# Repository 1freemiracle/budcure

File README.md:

# The Cannaster reinvisions the post-harvest workflow. The BudCureBox and Cannaster allows for automated control over the moisture content of the harvest, promising distinct differences in auroma and flavor. 

<div align="center">

</div>

## In the BudCureBox, you can estimate the moisture content by the weight loss due to evaporation. The weight is tracked from harvest and a target weight is calculated. This weight is used to know when to take the nugs off the branch and put into the Cannaster, when about 65% of the initial weight is lost.

<div align="center">

</div>

> The BudCure Box provides a stable environment for the buds to slowly dry. 

## The Cannaster takes mostly dry nugs and gets them to the perfect moisture content for canning. The vacuum brings moisture out from inside the nugs, drying them quickly and evenly to a precise moisture content. 

<div align="center">

</div>
> The Cannaster dials in the moisture content of the buds in preparation for canning.

## The machines are built out of laser cut or 3D printed parts, and I have included up to date files on how to build one, including eagle PCB and fusion 360 files.

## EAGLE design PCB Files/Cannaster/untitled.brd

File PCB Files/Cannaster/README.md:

# PCB files for the Cannaster
## 4 stepper motors plug directly into the board, with the L293D stepper driver chip. I'm also plugging into i2c humidity and pressure sensor, the BMP280 + AHT20, along with an OLED with rotary encoder display. The cannaster is powered by the wemos d1 mini.

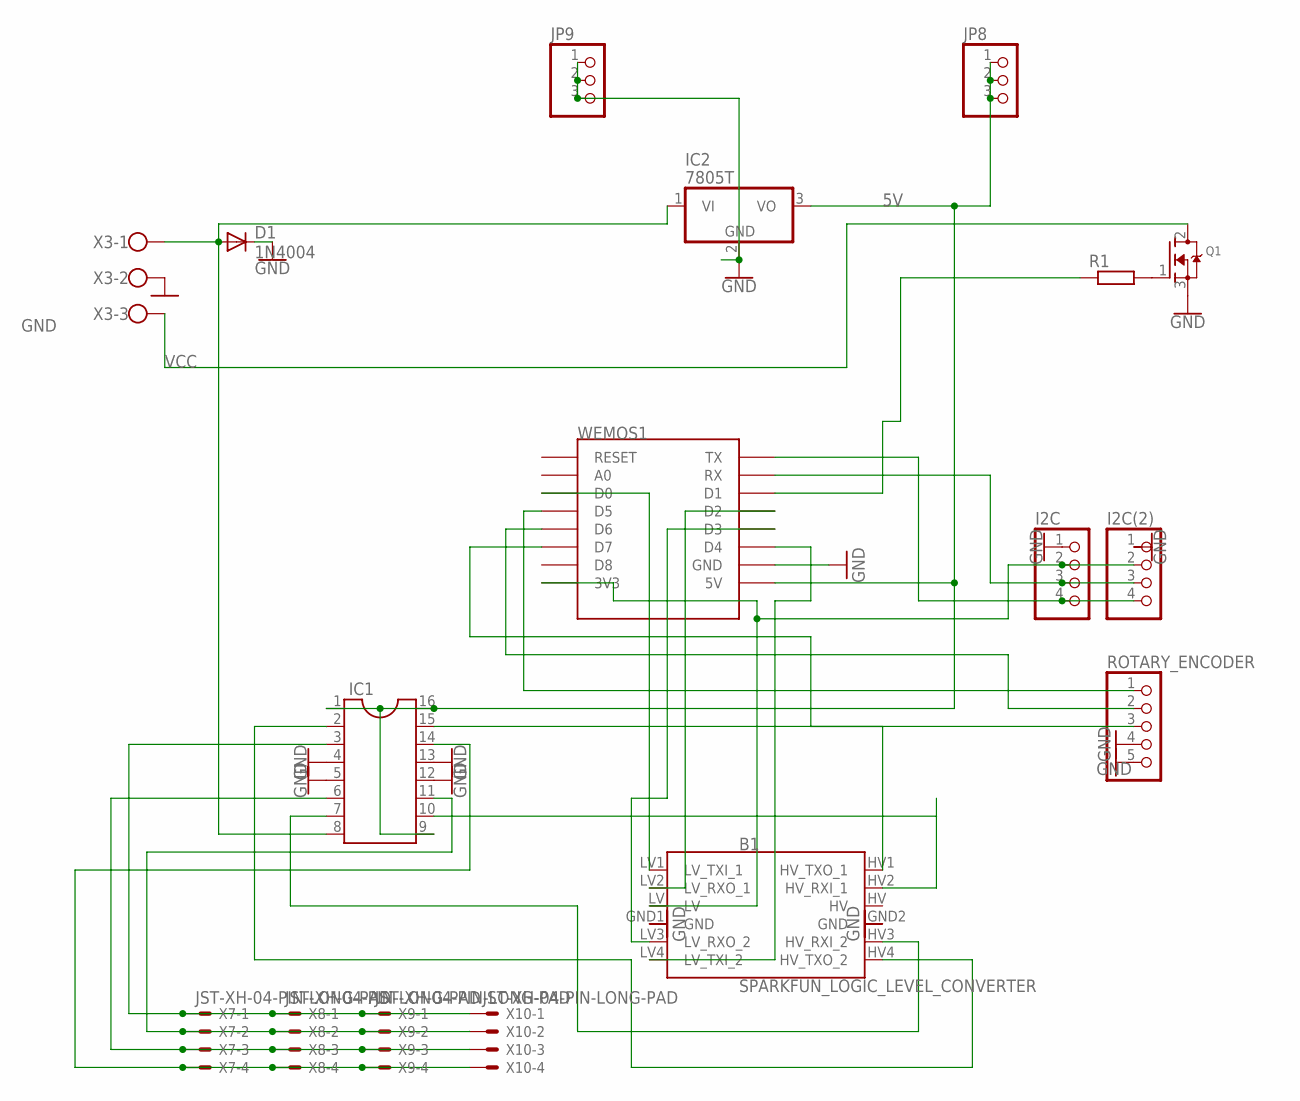
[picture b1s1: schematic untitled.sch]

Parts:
B1: SPARKFUN_LOGIC_LEVEL_CONVERTER
D1: 1N4004; DO41-10
I2C, I2C(2): PINHD-1X4; 1X04
IC1: DIL16
IC2: 7805T; TO220H
JP8, JP9: PINHD-1X3; 1X03
Q1: MOSFET-NGDS_TO220V; TO220V
R1: R-EU_0207/7; 0207/7
ROTARY_ENCODER: PINHD-1X5; 1X05
WEMOS1: WEMOS-D1-MINI
X3: W237-103
X7, X8, X9, X10: JST-XH-04-PIN-LONG-PAD; JST-XH-04-PACKAGE-LONG-PAD

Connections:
5V: IC1.1, IC1.9, IC1.16, IC2.3 (VO), JP8.1, JP8.2, JP8.3, WEMOS1.5V
GND: B1.GND1 (GND), B1.GND2 (GND), D1.C, I2C.1, I2C(2).1, IC1.4, IC1.5, IC1.12, IC1.13, IC2.2 (GND), JP9.1, JP9.2, JP9.3, Q1.3 (S), ROTARY_ENCODER.4, ROTARY_ENCODER.5, WEMOS1.GND, X3.2
HV: B1.HV
unnamed: IC1.3, X7.1, X8.1, X9.1, X10.1
unnamed: IC1.11, X7.2, X8.2, X9.2, X10.2
unnamed: B1.HV1 (HV_TXO_1), IC1.15
unnamed: IC1.14, X7.4, X8.4, X9.4, X10.4
unnamed: B1.LV1 (LV_TXI_1), WEMOS1.D0
unnamed: Q1.2 (D), X3.3
unnamed: I2C.4, I2C(2).4, WEMOS1.TX
unnamed: I2C.3, I2C(2).3, WEMOS1.RX
unnamed: B1.LV2 (LV_RXO_1), WEMOS1.D2
unnamed: Q1.1 (G), R1.2
unnamed: B1.LV3 (LV_RXO_2), WEMOS1.D3
unnamed: B1.LV4 (LV_TXI_2), WEMOS1.D4
unnamed: ROTARY_ENCODER.1, WEMOS1.D5
unnamed: ROTARY_ENCODER.2, WEMOS1.D6
unnamed: ROTARY_ENCODER.3, WEMOS1.D7
unnamed: R1.1, WEMOS1.D1
unnamed: B1.LV, I2C.2, I2C(2).2, WEMOS1.3V3
unnamed: B1.HV2 (HV_RXI_1), IC1.10
unnamed: B1.HV3 (HV_RXI_2), IC1.7
unnamed: B1.HV4 (HV_TXO_2), IC1.2
unnamed: IC1.6, X7.3, X8.3, X9.3, X10.3
VCC: D1.A, IC1.8, IC2.1 (VI), X3.1

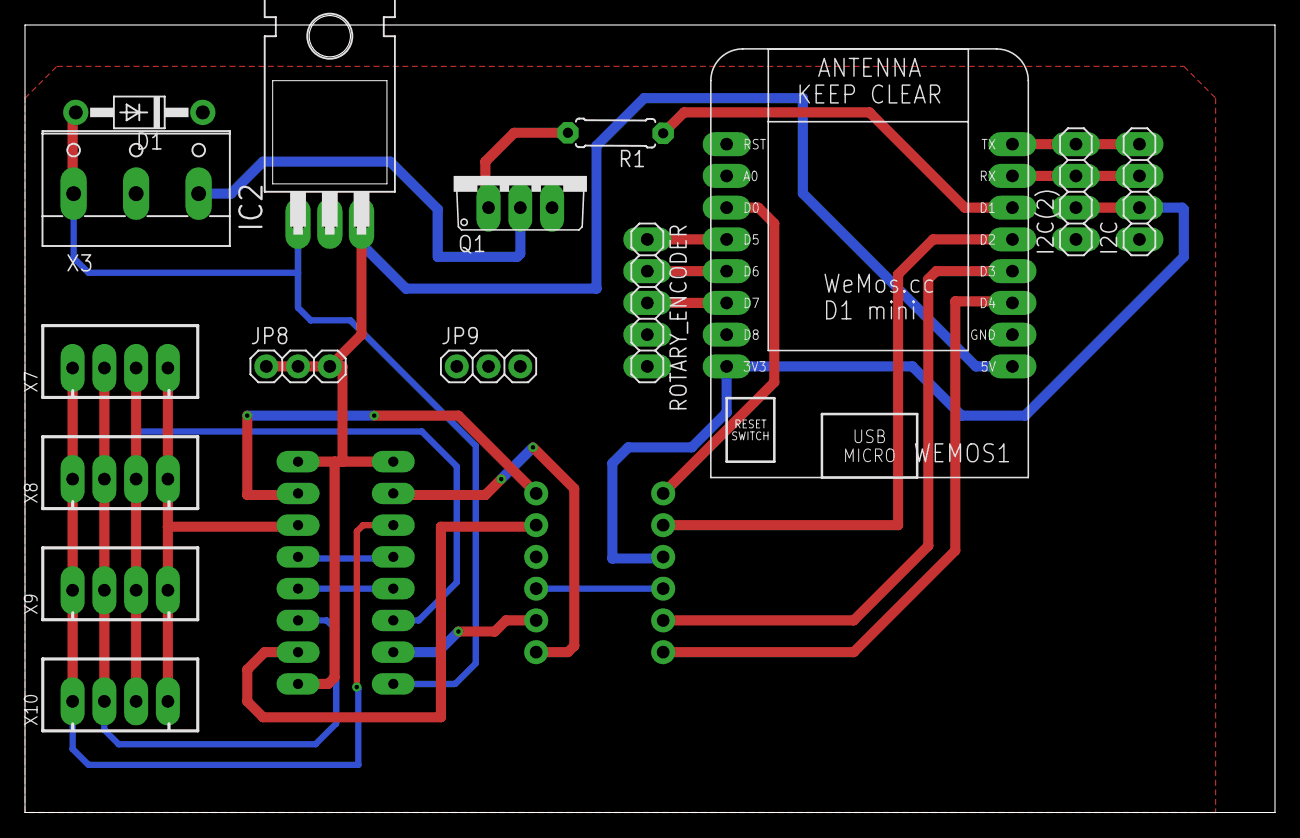
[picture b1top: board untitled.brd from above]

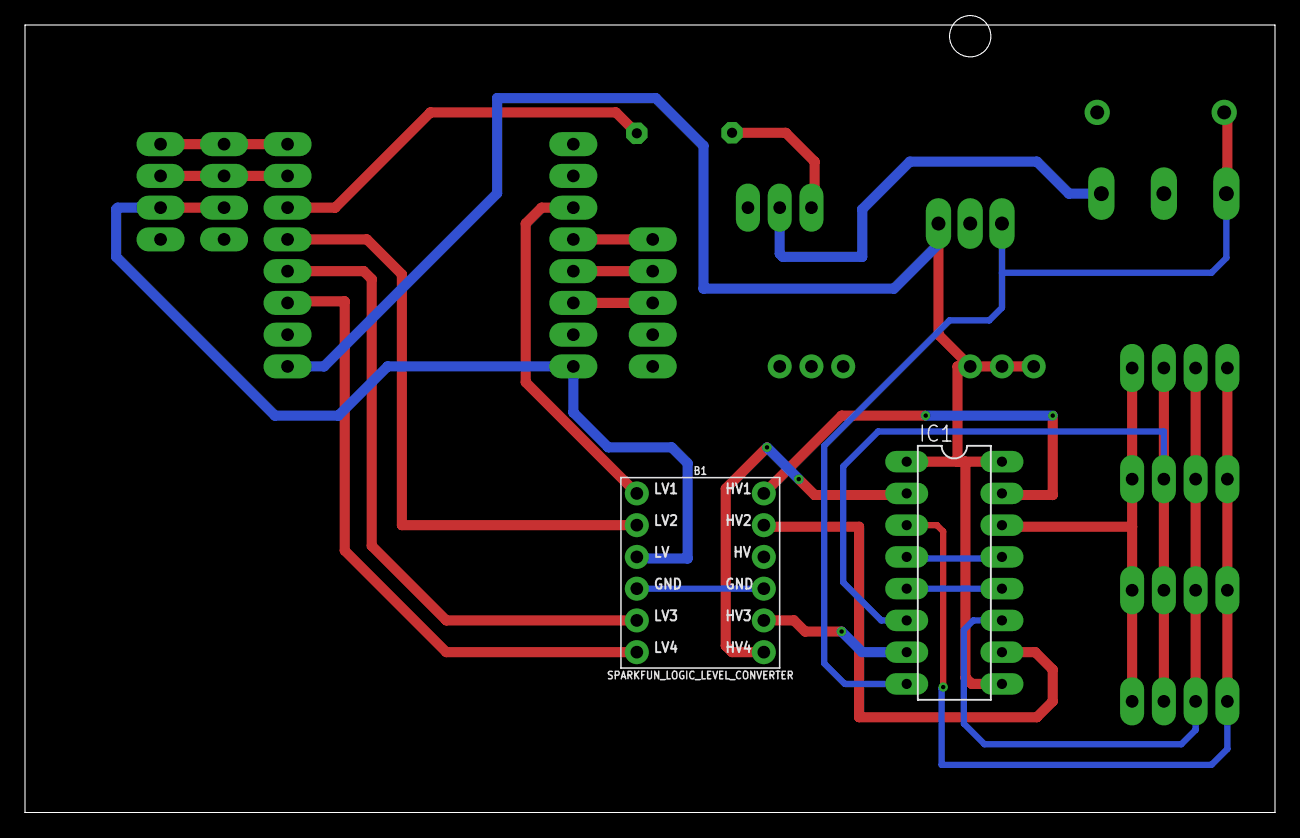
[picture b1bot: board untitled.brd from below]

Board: 2 copper layers, 100.0 x 63.0 mm, 17 parts (2 on the bottom side), 24 nets.

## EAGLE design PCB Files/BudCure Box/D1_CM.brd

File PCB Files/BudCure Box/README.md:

# PCB for the BudCure Box
## The BudCure Box pcb utilizes two mosfets, OLED/rotary encoder, i2c humidity sensor, load cell (with hx711), and a one wire temperature sensor for the TEC. 12V power runs the TEC and the fan while a 5v regulator supplies the Wemos.

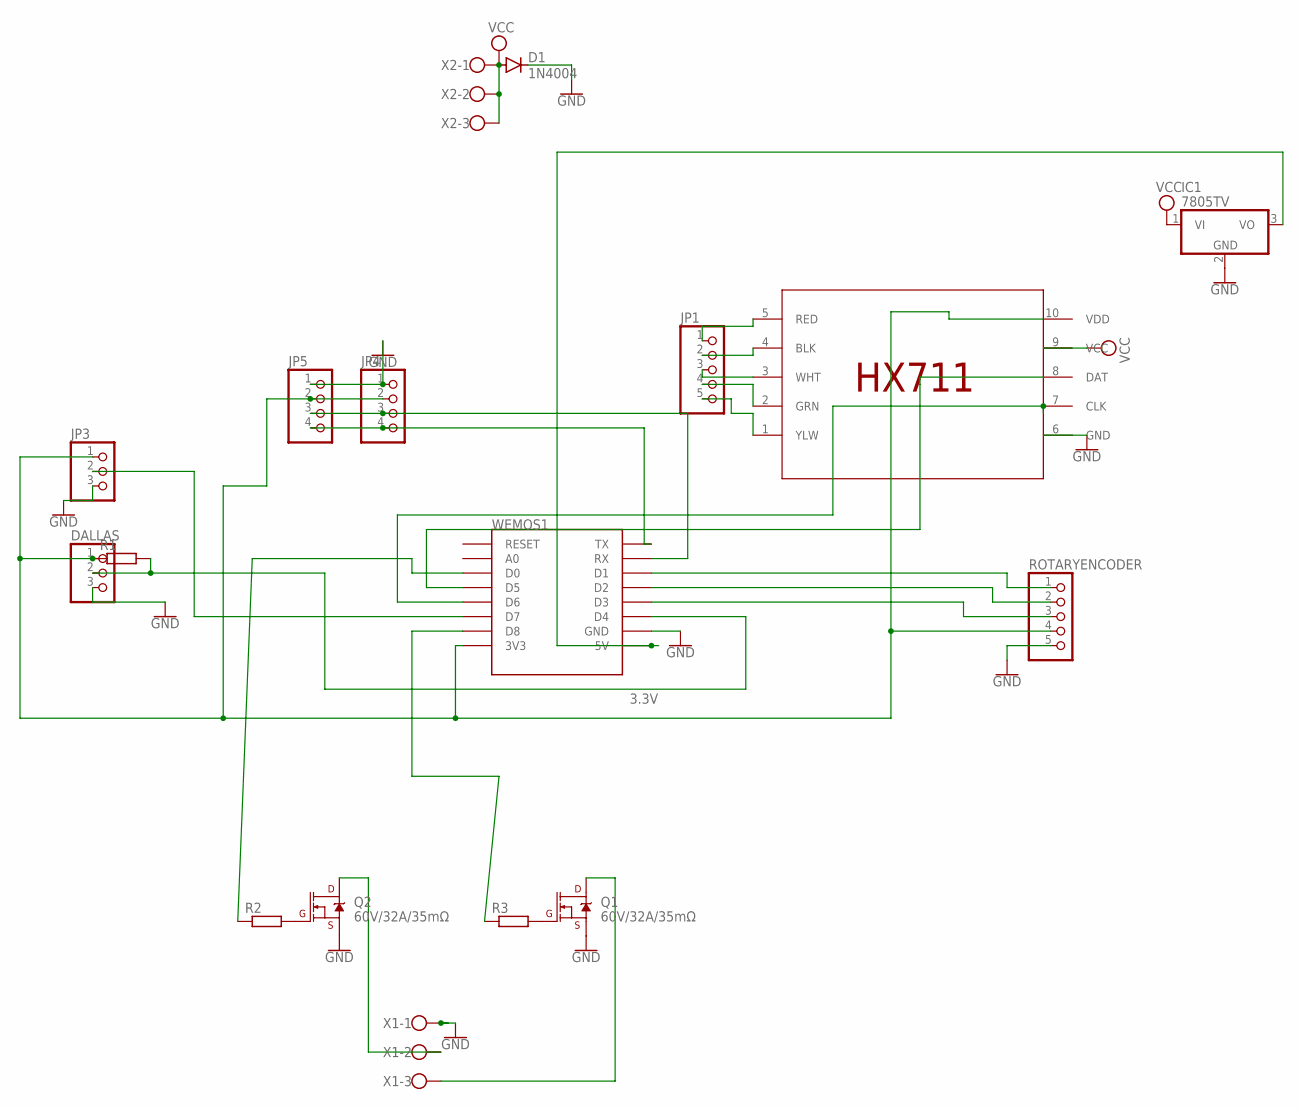
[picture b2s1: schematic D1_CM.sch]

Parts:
D1: 1N4004; DO41-10
DALLAS: PINHD-1X3; 1X03
IC1: 7805TV; TO220V
JP1: PINHD-1X5; 1X05
JP3: PINHD-1X3; 1X03
JP4, JP5: PINHD-1X4; 1X04
Q1, Q2: 60V/32A/35mΩ; TO220V
R1, R2, R3: R-EU_0207/7; 0207/7
ROTARYENCODER: PINHD-1X5; 1X05
U$1: DEVICY; FOOTSY
WEMOS1: WEMOS-D1-MINI
X1, X2: W237-103

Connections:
3.3V: DALLAS.1, JP3.1, JP4.2, JP5.2, R1.1, ROTARYENCODER.4, U$1.10 (VDD), WEMOS1.3V3
GND: D1.C, DALLAS.3, IC1.2 (GND), JP3.3, JP4.1, JP5.1, Q1.3 (S), Q2.3 (S), ROTARYENCODER.5, U$1.6 (GND), WEMOS1.GND, X1.1
unnamed: JP1.1, U$1.5 (RED)
unnamed: JP1.2, U$1.4 (BLK)
unnamed: JP1.3, U$1.3 (WHT)
unnamed: JP1.4, U$1.2 (GRN)
unnamed: JP1.5, U$1.1 (YLW)
unnamed: DALLAS.2, R1.2, WEMOS1.D4
unnamed: Q2.1 (G), R2.2
unnamed: JP4.3, JP5.3, WEMOS1.RX
unnamed: JP4.4, JP5.4, WEMOS1.TX
unnamed: Q1.1 (G), R3.2
unnamed: ROTARYENCODER.2, WEMOS1.D2
unnamed: ROTARYENCODER.1, WEMOS1.D1
unnamed: R2.1, WEMOS1.D0
unnamed: R3.1, WEMOS1.D8
unnamed: Q2.2 (D), X1.2
unnamed: Q1.2 (D), X1.3
unnamed: U$1.8 (DAT), WEMOS1.D5
unnamed: U$1.7 (CLK), WEMOS1.D6
unnamed: JP3.2, WEMOS1.D7
unnamed: ROTARYENCODER.3, WEMOS1.D3
unnamed: IC1.3 (VO), WEMOS1.5V
VCC: D1.A, IC1.1 (VI), U$1.9 (VCC), X2.1, X2.2, X2.3

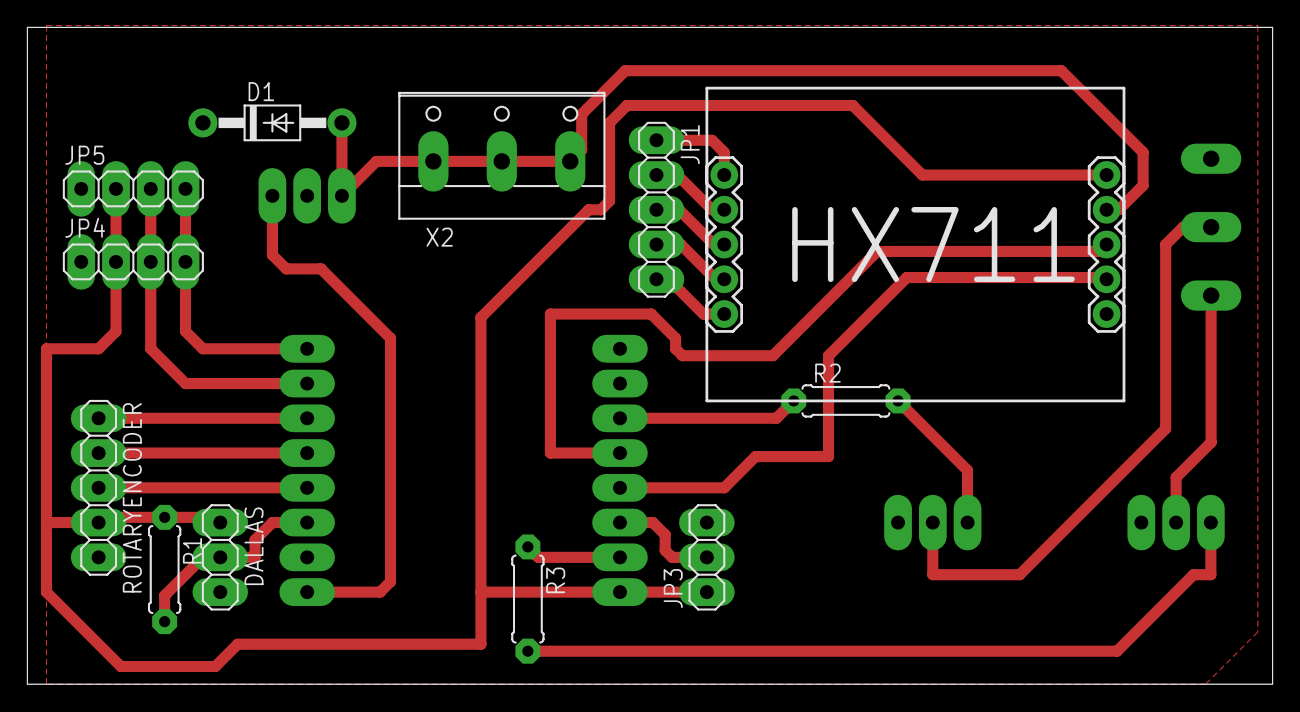
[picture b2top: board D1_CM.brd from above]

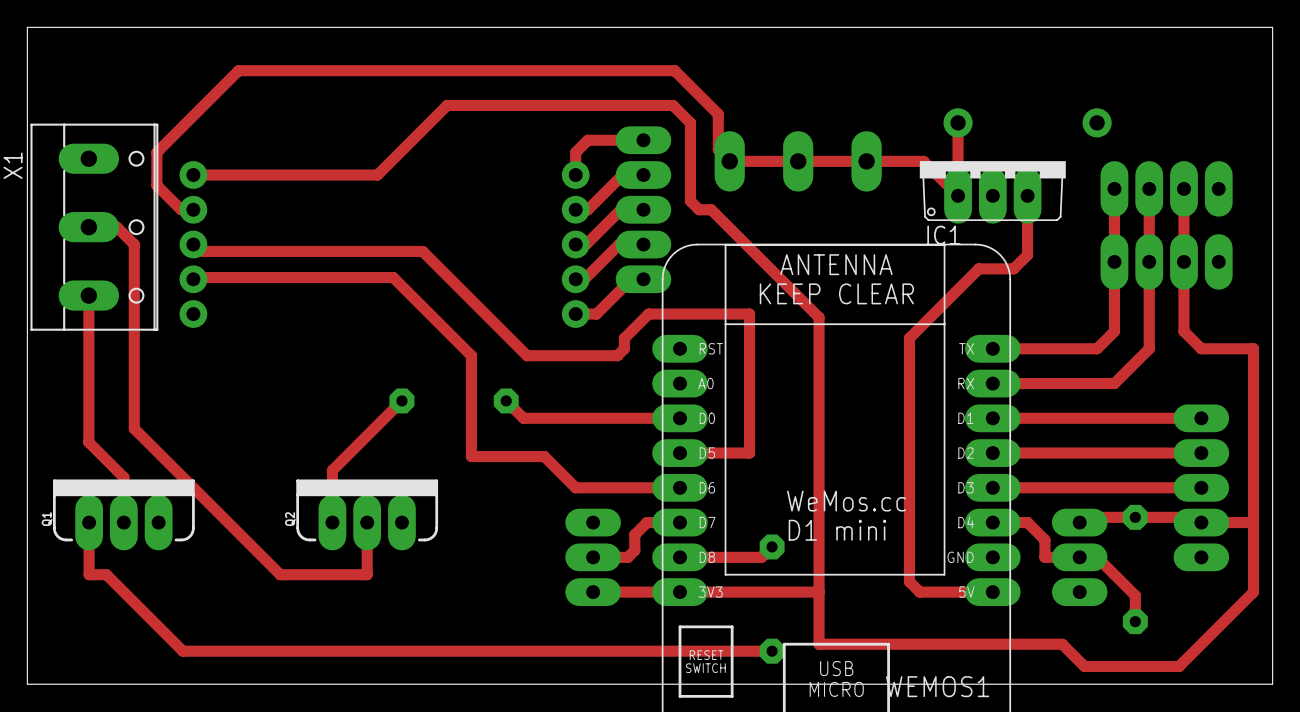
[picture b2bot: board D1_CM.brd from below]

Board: 2 copper layers, 91.0 x 48.0 mm, 17 parts (5 on the bottom side), 24 nets.

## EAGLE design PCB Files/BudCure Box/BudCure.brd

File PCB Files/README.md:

# EAGLE CAD FILES
## The BudCure Box and Cannaster utilize the Arduino Nano.

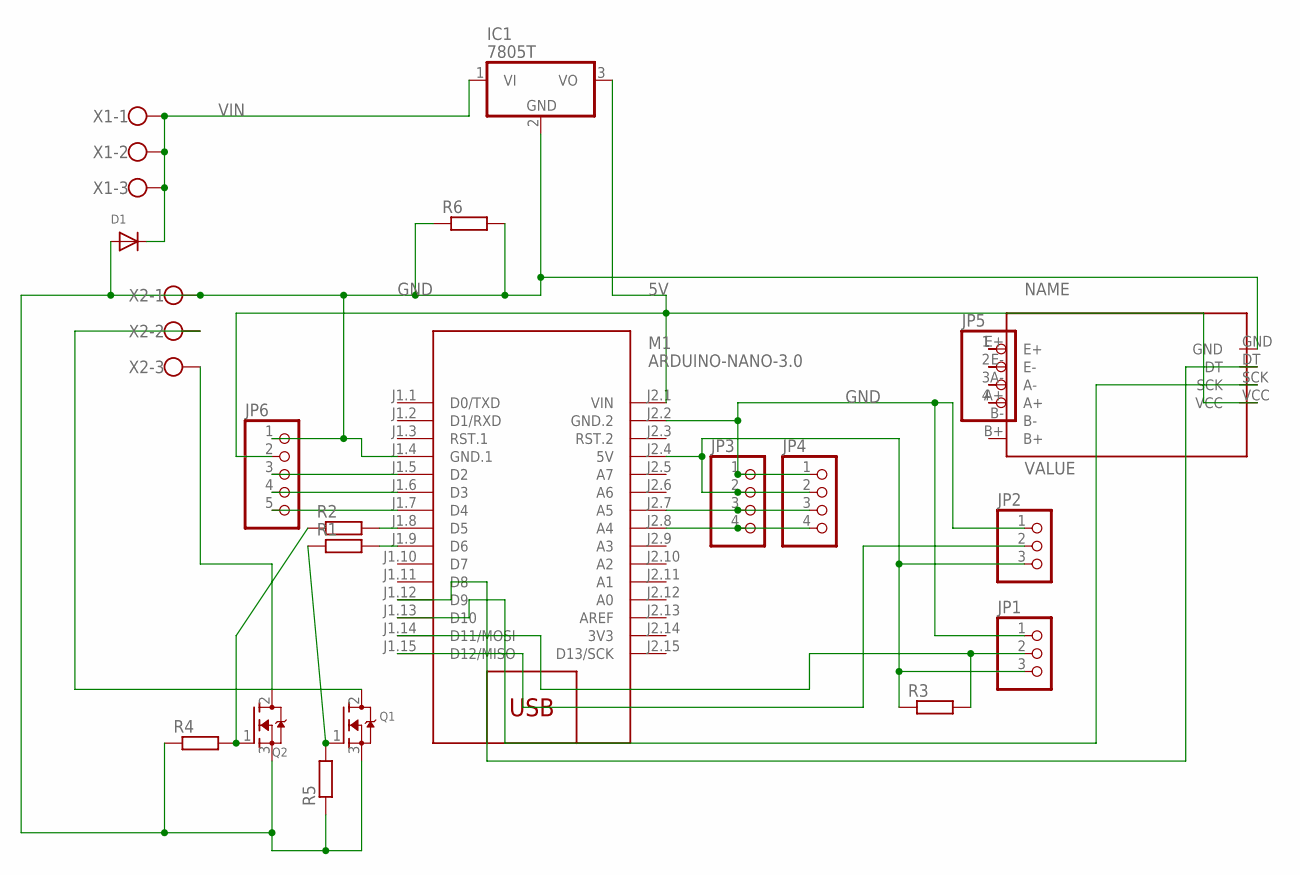
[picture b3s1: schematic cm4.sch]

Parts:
D1: DIODEDO-1N4148; DO-1N4148
IC1: 7805T; TO220H
JP1, JP2: PINHD-1X3; 1X03
JP3, JP4, JP5: PINHD-1X4; 1X04
JP6: PINHD-1X5; 1X05
M1: ARDUINO-NANO-3.0
Q1, Q2: MOSFET-NGDS_TO220V; TO220V
R1, R2, R3, R4, R5, R6: R-EU_0207/7; 0207/7
U$1: HX711A; HX711
X1, X2: W237-103

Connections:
3V3: M1.J2.14 (3V3)
5V: IC1.3 (VO), JP6.2, M1.J2.1 (VIN), U$1.VCC
GND: D1.A, IC1.2 (GND), JP1.1, JP2.1, JP3.1, JP4.1, JP6.1, M1.J1.4 (GND.1), M1.J2.2 (GND.2), Q1.3 (S), Q2.3 (S), R4.1, R5.1, R6.1, R6.2, U$1.GND, X2.1
unnamed: M1.J1.8 (D5), R2.2
unnamed: M1.J1.9 (D6), R1.2
unnamed: JP6.3, M1.J1.5 (D2)
unnamed: JP6.4, M1.J1.6 (D3)
unnamed: JP5.1, U$1.E+
unnamed: JP5.2, U$1.E-
unnamed: JP1.3, JP2.3, JP3.2, JP4.2, M1.J2.4 (5V), R3.1
unnamed: Q1.1 (G), R1.1, R5.2
unnamed: Q2.1 (G), R2.1, R4.2
unnamed: Q2.2 (D), X2.3
unnamed: Q1.2 (D), X2.2
unnamed: JP6.5, M1.J1.7 (D4)
unnamed: JP5.3, U$1.A-
unnamed: JP5.4, U$1.A+
unnamed: M1.J1.12 (D9), U$1.DT
unnamed: M1.J1.13 (D10), U$1.SCK
unnamed: JP3.3, JP4.3, M1.J2.7 (A5)
unnamed: JP3.4, JP4.4, M1.J2.8 (A4)
unnamed: JP1.2, M1.J1.14 (D11/MOSI), R3.2
unnamed: JP2.2, M1.J1.15 (D12/MISO)
VIN: D1.C, IC1.1 (VI), X1.1, X1.2, X1.3

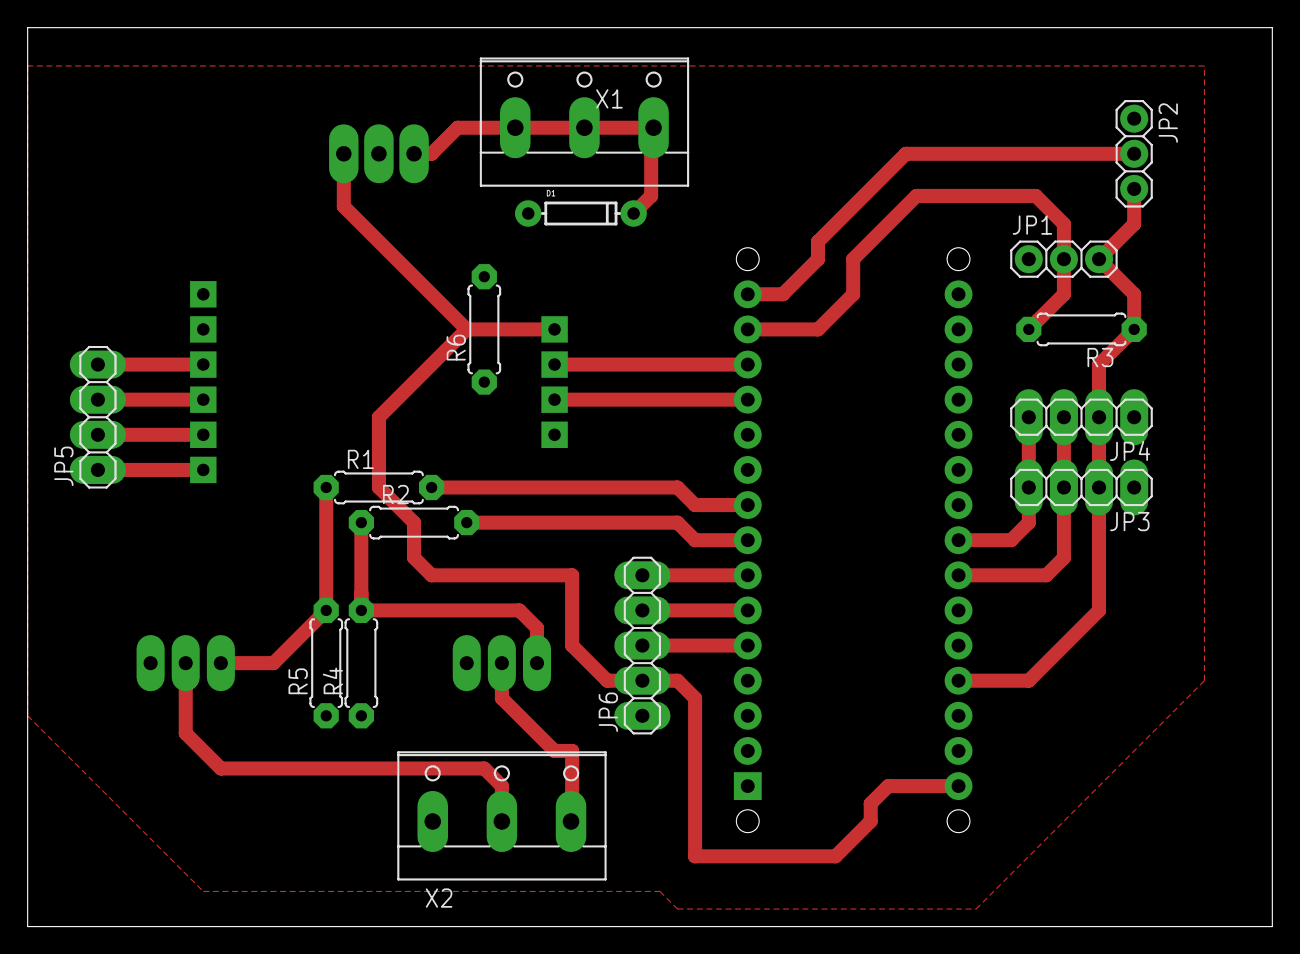
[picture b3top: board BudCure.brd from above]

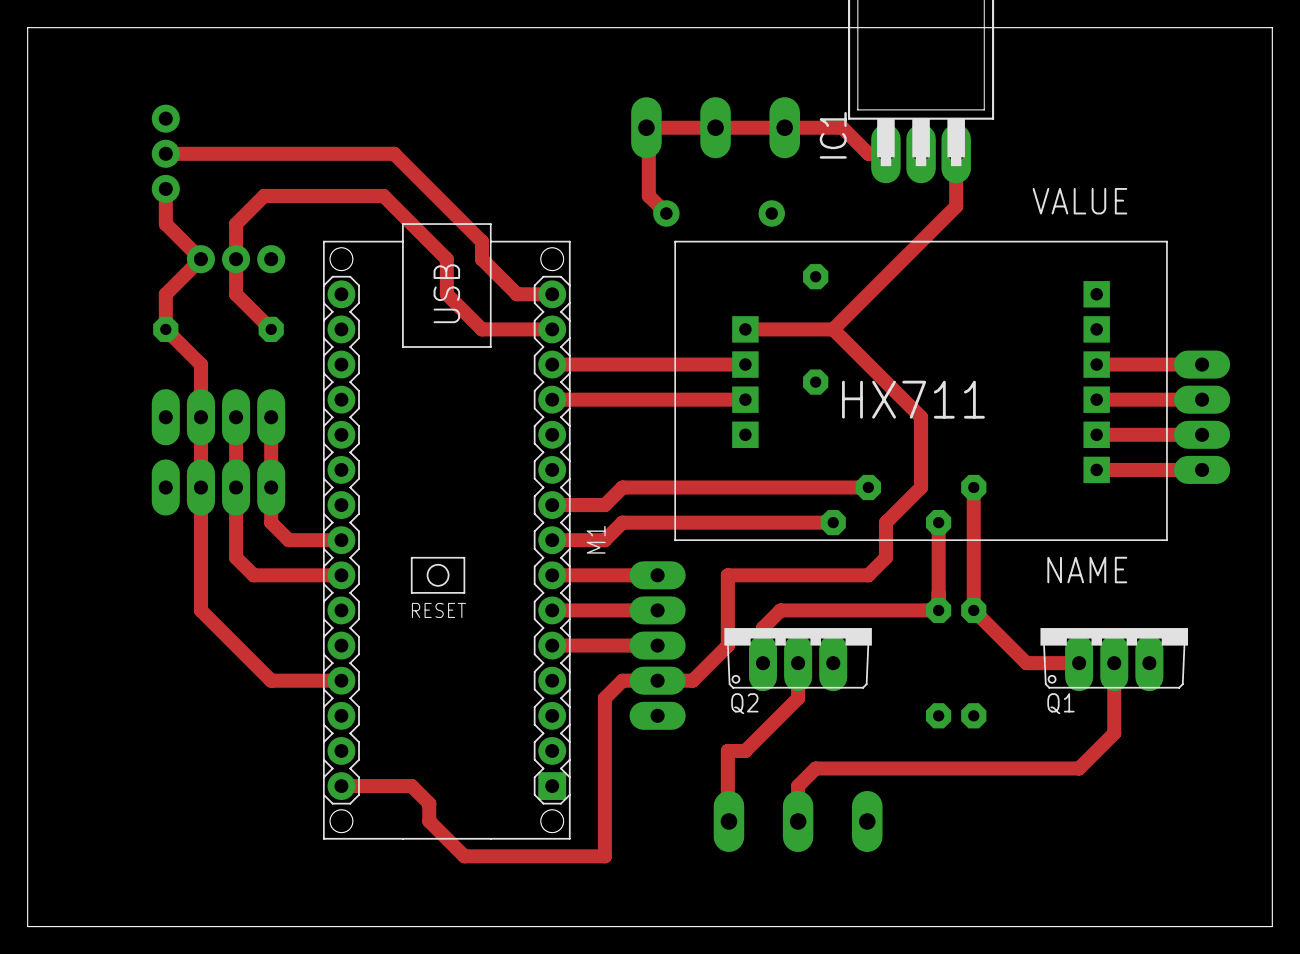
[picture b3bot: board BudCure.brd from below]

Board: 2 copper layers, 90.0 x 65.0 mm, 20 parts (5 on the bottom side), 23 nets.

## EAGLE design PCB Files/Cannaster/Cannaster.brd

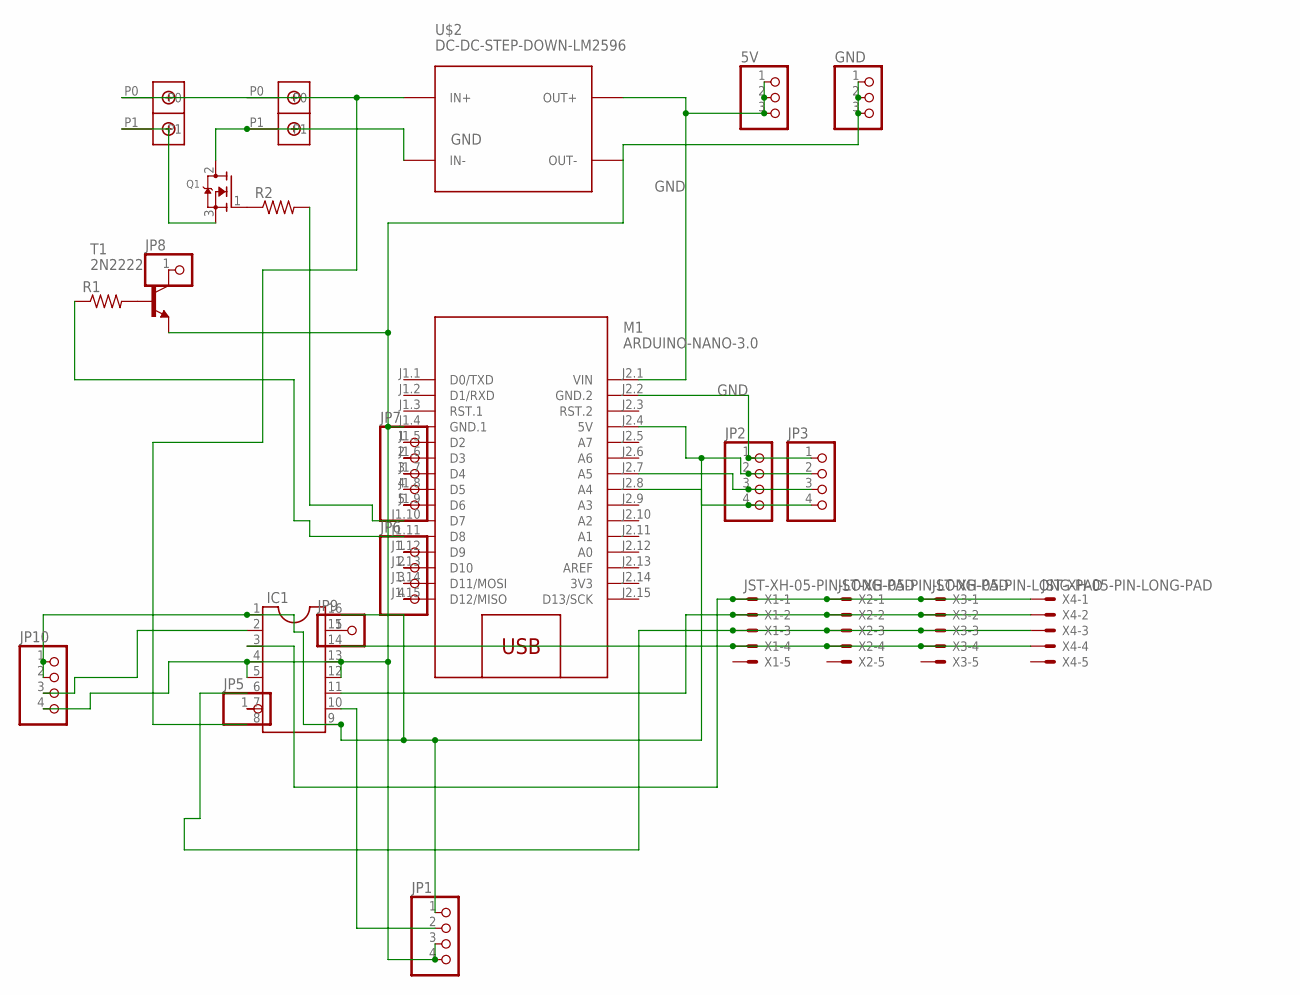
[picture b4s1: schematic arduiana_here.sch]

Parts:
5V: PINHD-1X3; 1X03
GND: PINHD-1X3; 1X03
IC1: DIL16S; SOCKET-16
JP1, JP2, JP3, JP6, JP10: PINHD-1X4; 1X04
JP5, JP8, JP9: PINHD-1X1; 1X01
JP7: PINHD-1X5; 1X05
M1: ARDUINO-NANO-3.0
POWER: DBCONN-1X2
PUMP: DBCONN-1X2
Q1: MOSFET-NGDS_TO220V; TO220V
R1, R2: R-US_0204/5; 0204/5
T1: 2N2222; TO92-EBC-OVAL
U$2: DC-DC-STEP-DOWN-LM2596
X1, X2, X3, X4: JST-XH-05-PIN-LONG-PAD; JST-XH-05-PACKAGE-LONG-PAD

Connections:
3V3: M1.J2.14 (3V3)
GND: GND.1, GND.2, GND.3, IC1.4, IC1.5, IC1.12, IC1.13, JP1.3, JP1.4, JP2.1, JP3.1, JP10.4, M1.J1.4 (GND.1), M1.J2.2 (GND.2), POWER.P1, Q1.2 (D), T1.E, U$2.IN-, U$2.OUT-
unnamed: M1.J1.11 (D8), R1.1
unnamed: IC1.2, JP10.3
unnamed: M1.J1.10 (D7), R2.2
unnamed: JP8.1, T1.C
unnamed: R1.2, T1.B
unnamed: Q1.1 (G), R2.1
unnamed: PUMP.P1, Q1.3 (S)
unnamed: 5V.1, 5V.2, 5V.3, M1.J2.1 (VIN), U$2.OUT+
unnamed: JP2.4, JP3.4, M1.J2.8 (A4)
unnamed: JP2.3, JP3.3, M1.J2.7 (A5)
unnamed: JP7.1, M1.J1.5 (D2)
unnamed: JP6.1, M1.J1.12 (D9)
unnamed: JP6.2, M1.J1.13 (D10)
unnamed: JP7.2, M1.J1.6 (D3)
unnamed: IC1.7, JP5.1
unnamed: IC1.10, JP1.2
unnamed: IC1.15, JP9.1
unnamed: IC1.1, IC1.9, IC1.16, JP1.1, JP2.2, JP3.2, JP10.1, JP10.2, M1.J2.4 (5V)
unnamed: IC1.3, X1.1, X2.1, X3.1, X4.1
unnamed: IC1.6, X1.3, X2.3, X3.3, X4.3
unnamed: IC1.11, X1.2, X2.2, X3.2, X4.2
unnamed: IC1.14, X1.4, X2.4, X3.4, X4.4
unnamed: JP7.3, M1.J1.7 (D4)
unnamed: JP7.4, M1.J1.8 (D5)
unnamed: JP7.5, M1.J1.9 (D6)
unnamed: JP6.3, M1.J1.14 (D11/MOSI)
unnamed: JP6.4, M1.J1.15 (D12/MISO)
PUMP: IC1.8, POWER.P0, PUMP.P0, U$2.IN+

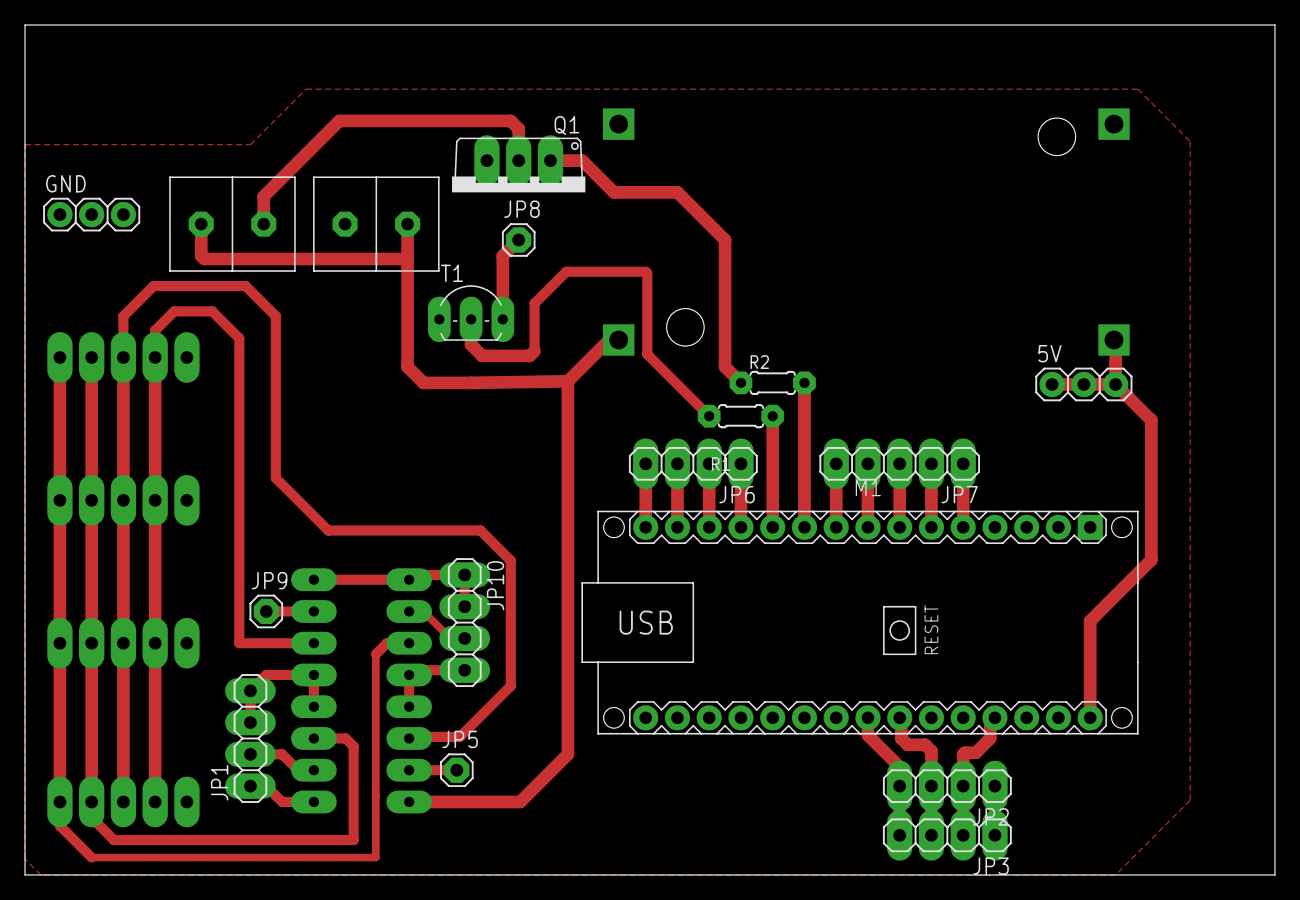
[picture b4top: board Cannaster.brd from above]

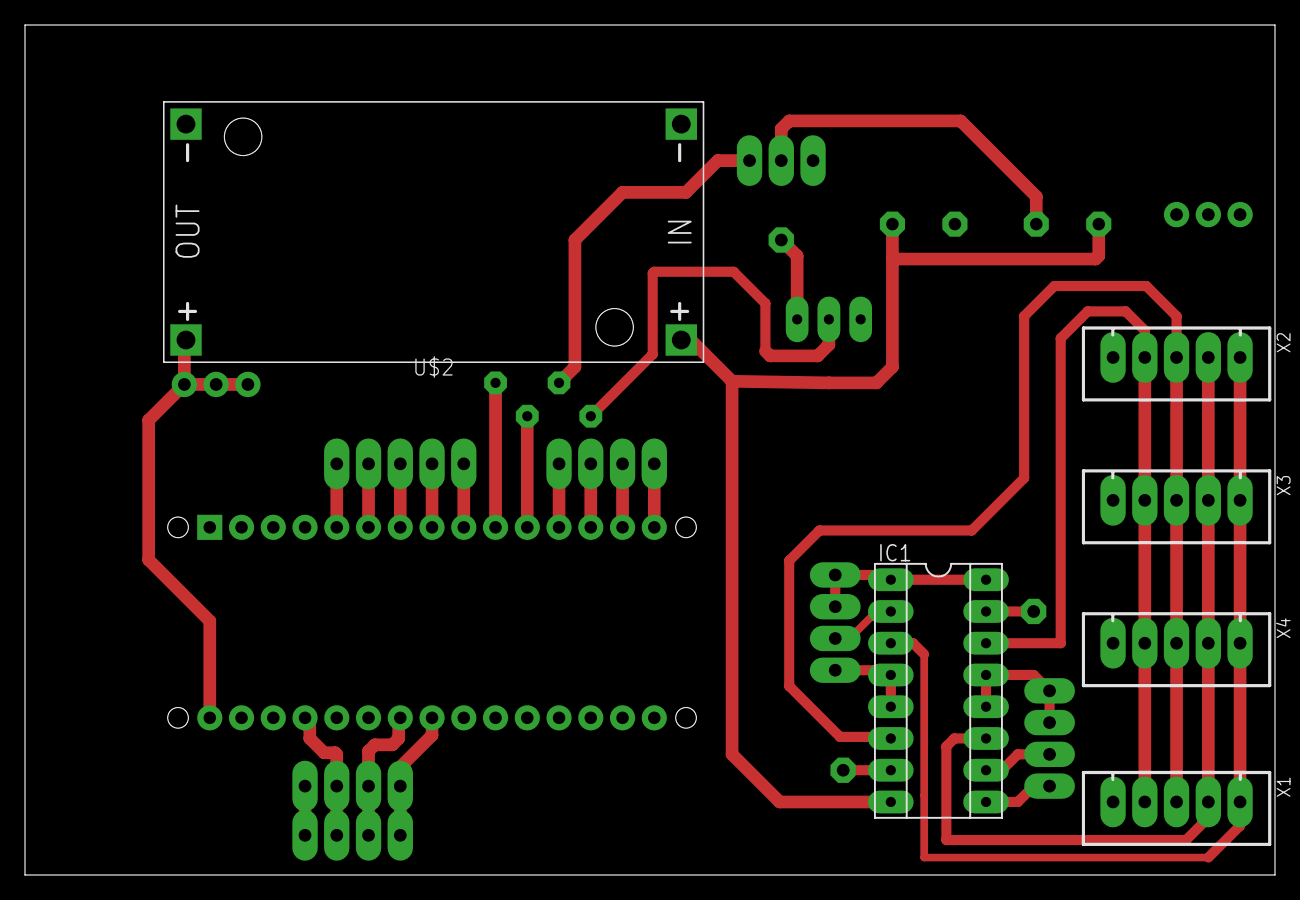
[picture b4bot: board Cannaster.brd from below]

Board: 2 copper layers, 100.0 x 68.0 mm, 24 parts (6 on the bottom side), 29 nets.

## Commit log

2024-07-14 Create Arduino Code
2024-07-14 Create fusion 360 files
2024-07-14 Rename readme.dm to readme.md
2024-07-15 Rename arduiana_here.brd to Cannaster.brd
2024-07-15 Rename arduiana_here.sch to Cannaster.sch
2024-07-15 Rename cm4.brd to BudCure.brd
2024-07-15 Rename cm4.sch to BudCure.sch
2024-07-15 Rename CM.ino to BudCure.ino
2024-07-15 Rename arduiana_NOW.ino to Cannaster.ino
2024-08-12 Create encoder_functions
2024-12-22 Rename untitled.brd to cannaster.brd
2024-12-22 Rename Cannaster.brd to void.brd
2024-12-22 Rename Cannaster.sch to void.sch
2024-12-22 Rename untitled.sch to cannaster.sch
2024-12-22 Update encoder_functions
2024-12-22 Rename silicon_gasket_mold.f3d to void.f3d
2024-12-22 Rename Cannaster.f3z to void.f3z

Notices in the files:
parts and their libraries:
diy-modules: Released under the Creative Commons Attribution 4.0 International License: http://creativecommons.org/licenses/by/4.0
SparkFun-DiscreteSemi: Licensing: Creative Commons ShareAlike 4.0 International - https://creativecommons.org/licenses/by-sa/4.0
